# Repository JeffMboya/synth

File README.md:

<div align="center">

### Design circuit boards as code.

Turn text-based circuit designs into KiCad schematics, PCB layouts, and bills of materials.

Open source. Built for engineers and AI agents.

[Quick Start](#quick-start) · [Features](#features) · [Examples](#examples) · [Documentation](https://absmach.eu/docs/synth/user-guide/quick-start/) · [Contributing](#contributing)

</div>

## Introduction

Synth is an open-source compiler for electronic circuit boards. Describe your components, their connections, and board constraints in **SynthSpec**, a text-based design language. Synth checks the design and generates KiCad schematics, PCB layouts, and a bill of materials.

This brings a software development workflow to hardware: edit designs in your usual editor, review changes in Git, and run automated checks. Your `.synth` files capture the design intent; the schematic and board layout are generated outputs you can inspect in KiCad.

Engineers can use Synth from the command line. AI agents can use its **Model Context Protocol (MCP)** server to find components, validate circuits, and generate outputs through the same compiler, with structured diagnostics to guide corrections.

## Release checks

For CI and agent workflows, `synth check DESIGN.synth --json` is the single
deterministic, model-free gate for compiler validation and DRC. Add `--fab` to
require a complete KiCad manufacturing export and receive SHA-256 hashes for
the emitted files. A timed-out or unavailable physical stage is reported as
`unknown` and blocks the command; it is never treated as a pass.

Stages that shell out to `kicad-cli` are tri-state, because a check that
could not run is neither a pass nor a failure:

| Status    | Meaning                                                                 |
| --------- | ----------------------------------------------------------------------- |
| `pass`    | The tool ran and reported no blocking violations.                       |
| `fail`    | The tool ran and rejected the design.                                   |
| `unknown` | No evidence. Missing or unsupported `kicad-cli`, a missing symbol/footprint library, a crash, a timeout, or an unreadable report. |

`unknown` blocks exactly as `fail` does, and `--force` does not override it —
it overrides Synth's own findings, not the absence of verification. Likewise,
unconnected pads and KiCad DRC errors block a release export, and `--force`
does not override that. Each
`unknown` reports the tool, its version, the exact command, its stderr, and a
machine-stable reason (`not_installed`, `timeout`, `command_failed`,
`report_malformed`, `unsupported_version`, ...). `synth check --fab` embeds
that evidence under `stages.manufacturing.native`; `synth export-kicad
--verification-report FILE` writes it directly.

A plain `synth export-kicad` still works with no KiCad installed: it records
the `unknown` and sets `release_ready: false`, but does not block, since
nothing about that output claims to have been verified. Requesting
verification — `--validate-erc`, or any of `--gerbers`/`--drill`/`--step` —
makes an `unknown` blocking. Set `KICAD_CLI` to point at a specific build, and
`SYNTH_KICAD_CLI_TIMEOUT_SECS` to change the per-run budget (default 300s).

### Export overrides

`--force` and `--allow-unverified-parts` let development proceed past
findings that would otherwise stop an export. Every use is recorded in
`<out>/release.json` with the exact flag, the diagnostic it suppressed, the
affected parts, and the reviewer state of every part on the board:

| Field | Meaning |
| --- | --- |
| `release_ready` | `false` whenever any override was used. Derived, not settable. |
| `production_status` | `production` or `untrusted`. |
| `overrides[]` | flag, code, affected parts, and the consequence in plain words. |
| `reviewer_state[]` | per part: `reviewed_by`, `reviewed_at`, and whether it is reviewed. |

Human output on these paths leads with `UNTRUSTED / NOT FOR FABRICATION`.

`synth check --fab` reads that manifest and refuses a package carrying
overrides. To proceed, record who authorized it and why:

```bash
synth check DESIGN.synth --fab \
  --override-exception "prototype run, not customer hardware" \
  --authorized-by "a release manager"
```

An exception authorizes the run; it does not clean the package.
`release_ready` stays `false` and `production_status` stays `untrusted`,
because an authorization is a decision about risk rather than evidence the
risk is gone.

For CI and release gates, `synth export-kicad --safe` is the mode with no
override path: it refuses to sit beside `--force` or
`--allow-unverified-parts`, and then checks that the package it produced is
actually clean.

## Why Synth?

- **Review hardware changes in Git.** Components, connections, and constraints are text, making design intent visible in diffs and pull requests.
- **Check designs as you build.** Structured diagnostics identify problems and provide source locations and suggested fixes where available.
- **Keep outputs reproducible.** A typed compiler pipeline and deterministic placement and routing make generated artifacts repeatable.
- **Work with KiCad.** Export schematics, PCBs, and BOMs for inspection and downstream workflows.
- **Give agents concrete tools.** Expose validation, registry search, placement, routing, and export through MCP.

## How It Works

```mermaid
flowchart LR
    source["SynthSpec source"] --> compiler["Parse & resolve"]
    compiler --> checks["Validate"]
    checks --> layout["Place & route"]
    layout --> export["KiCad project & BOM"]
    checks --> feedback["Diagnostics & fixes"]
    feedback --> source
```

Synth resolves parts from a component registry and lowers the source into a typed board representation. Compiler stages use that shared representation for electrical checks, layout, routing, and export. A local browser viewer displays the schematic and diagnostics as you edit.

## Features

| Area               | Capabilities                                                                                                 |
| ------------------ | ------------------------------------------------------------------------------------------------------------ |
| Design language    | SynthSpec parser, typed board IR, components, connections, differential pairs, keepouts, and placement hints |
| Validation         | Electrical-rule checks, design-rule checks, structured diagnostics, and SMT-backed quantitative fixes        |
| Layout and routing | Deterministic schematic layout, component placement, and multilayer routing                                  |
| KiCad integration  | Project, schematic, PCB, and BOM export; optional fabrication outputs through `kicad-cli`                    |
| Component registry | Versioned parts, project and user overlays, search, import, and authoring tools                              |
| Developer tools    | CLI, live browser preview, JSON diagnostics, and an MCP server for agent integration                         |

## Quick Start

Use a current stable Rust toolchain with Cargo. Run the following from a local checkout:

```bash
git clone https://github.com/absmach/synth.git
cd synth
cargo build -p synth-cli
cargo run -p synth-cli -- --help
```

Validate the minimal example and export a KiCad project:

```bash
cargo run -p synth-cli -- validate fixtures/designs/hello.synth
cargo run -p synth-cli -- export-kicad fixtures/designs/hello.synth --out output/hello
```

The minimal example declares an empty two-layer board. Use the [example designs](#examples) to explore circuits with components and connections.

For machine-readable diagnostics:

```bash
cargo run -p synth-cli -- validate examples/env_logger.synth --format json
```

Open exported projects in KiCad. Optional Gerber, drill, and STEP exports require `kicad-cli`; see the [KiCad workflow guide](docs/kicad-workflows.md) for export and review details.

### Live Preview

Build the browser assets using the prerequisites and instructions in the [viewer guide](crates/synth-web/README.md), then run:

```bash
cargo run -p synth-cli -- preview examples/env_logger.synth
```

Open the local URL printed by the command. Save changes to the `.synth` file in your editor to refresh the schematic and diagnostics.

### Agent Integration

Start the MCP server over standard input and output:

```bash
cargo run -p synth-cli -- mcp --stdio
```

Agents can retrieve the SynthSpec language reference, search the registry, validate designs, apply fixes, and invoke compiler stages. See the [MCP guide](crates/synth-mcp/README.md) for transports and tool details.

## Examples

| Design                                                                     | What it demonstrates                                                          |
| -------------------------------------------------------------------------- | ----------------------------------------------------------------------------- |
| [Hello](fixtures/designs/hello.synth)                                      | The smallest board declaration                                                |
| [Environmental logger](examples/env_logger.synth)                          | USB-C power, a regulator, an MCU, an environmental sensor, and a debug header |
| [Sensor logger](examples/sensor_logger.synth)                              | A larger design with dual I²C sensors, SPI flash, and status LEDs             |
| [Placement and differential pairs](examples/placement_and_diff_pair.synth) | Placement hints, differential-pair constraints, and keepout regions           |

Additional language and validation cases live in [fixtures](fixtures/designs/README.md). Part definitions live in the [component registry](registry/README.md).

### RP2350 development-board agent workflow

The repository includes the placement and FreeRouting workflow used to develop
an RP2350-class board, including clean-netlist routing, zone refill, layer
normalization, and compact-outline support. See the [RP2350 agent workflow](docs/rp2350-agent-workflow.md)
for setup instructions, prompts, review commands, and the pre-generated review
artifact in [examples/rp2350](examples/rp2350/).

_Pre-generated compact RP2350 routed review artifact; open the [KiCad board](examples/rp2350/rp2350_devboard_freerouting_clean.kicad_pcb)
for an interactive review._

## Documentation

- [KiCad workflows](docs/kicad-workflows.md) — exported projects, validation, BOMs, and fabrication outputs.
- [RP2350 agent workflow](docs/rp2350-agent-workflow.md) — clean-netlist FreeRouting, compact outlines, agent setup, and review prompts.
- [Schematic procedures](docs/schematic-procedures.md) — schematic generation and review.
- [Diagnostic reference](docs/diagnostics/README.md) — diagnostic codes and repair guidance.
- [Diagnostic protocol](docs/protocol-v1.0.md) — the machine-readable diagnostic format.
- [Component registry](registry/README.md) — part definitions and registry structure.
- [Browser viewer](crates/synth-web/README.md) — build and run the live preview.
- [MCP server](crates/synth-mcp/README.md) — agent tools and integration.

## Contributing

Contributions to the compiler, component registry, examples, and documentation are welcome. Use [issues](https://github.com/absmach/synth/issues) to report bugs or discuss a change, and submit a pull request with a focused description and relevant validation.

Before submitting code, run the workspace checks:

```bash
make verify
```

This checks formatting, compilation, Clippy lints, the workspace tests, and registry tests. Run `make help` to see individual development commands.

## License

Synth is licensed under the [Apache License 2.0](LICENSE).

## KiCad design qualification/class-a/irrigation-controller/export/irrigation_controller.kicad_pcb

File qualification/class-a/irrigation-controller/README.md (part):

# Irrigation controller

A two-zone irrigation controller: 12 V in through a polyfuse, an AO3401A
reverse blocker with a gate clamp and an SMAJ13A TVS, an MP2307 buck to 3.3 V,
an STM32G030, two low-side solenoid drivers, two switched resistive soil probes,
a flow-pulse input, an I2C header, an ambient light sensor and an EEPROM, an SWD
header, and rail decoupling, bleeders, snubbers, indicator LEDs and test points.
Two layers, JLCPCB, 75.1 x 65.4 mm, 126 components. There is no humidity sensor
on the board: a breakout attaches to the I2C header at address 0x44.

**Status:** the board is routed and released (45 of 45 nets; KiCad 10.0.7 reports 0 errors,
0 unconnected pads and 0 `silk_overlap` warnings with the library tables), three fresh exports are
identical, and the exported KiCad files, the DRC and ERC reports, a fabrication package and a
reproduction script are committed ([`export/`](export/), [`reports/`](reports/), [`fab/`](fab/),
[`reproduce/`](reproduce/)). Since SammyOina's review of 2026-10-30 10:57: `C_IN1` and `C_IN2` sit
3.3 and 3.5 mm from the regulator's input pin `U1.2`, inside the placement review's 4 mm, and the
review flags no decoupling capacitor; the five `silk_overlap` warnings and the one ERC error (`power_pin_not_driven` on `+12V_VALVE`) are gone; the numbers, hashes, renders and
files below all come from one export. Not done: JLCPCB's PCB DFM of this exact package and the SMT DFM and
quote, which need an upload (see "JLCPCB DFM results"), and an independent review of two registry parts. Nothing
here was built or tested on hardware.

## How this board was made

An agent produced the design; Synth's own tools and scripts then packed and
tidied it, and a reviewer's list of faults was worked through. Every step is
logged under [`agent-run/`](agent-run/).

| Step | What ran | Result |
|---|---|---|
| 1. The design | An agent from one prompt ([`agent-run/prompt.md`](agent-run/prompt.md)), driving `synth mcp` with Read, Write and Edit only, from an empty workspace ([`report.md`](agent-run/report.md), [`tool-calls.md`](agent-run/tool-calls.md)) | 86 components |
| 2. Compaction | `synth_compact_layout` in `gap` mode | 75.1 x 65.4 mm after the later steps, released |
| 3. Fill | Two agent runs ([`fill-pass-prompt.md`](agent-run/fill-pass-prompt.md), reports [1](agent-run/fill-pass-report-1.md), [2](agent-run/fill-pass-report-2.md)): parts in the voids, each wired to a real function | 26 parts added |
| 4. Placement advice | [`tools/apply_advice_par.py`](agent-run/tools/apply_advice_par.py) applies Synth's placement advice in released steps | two passes, 15 and 18 moves kept |
| 5. Review fixes | An agent from [`prompt-1-review-fixes.md`](agent-run/review-fixes/prompt-1-review-fixes.md), report [`report-1-review-fixes.md`](agent-run/review-fixes/report-1-review-fixes.md): the clamps, the input TVS, the SHT30, the crystal load capacitors, the valve current, the schematic groups | source fixed; the board did not release |
| 6. Release search | Scripts ([`release_search.py`](agent-run/tools/release_search.py), [`fix_one.py`](agent-run/tools/fix_one.py), [`fix_pairs.py`](agent-run/tools/fix_pairs.py), [`verify_gap.py`](agent-run/tools/verify_gap.py)) that move one or two parts near a blocking finding and keep a move only if the export releases | released |
| 7. Input MOSFET | An agent from [`prompt-2-input-mosfet.md`](agent-run/review-fixes/prompt-2-input-mosfet.md), report [`report-2-input-mosfet.md`](agent-run/review-fixes/report-2-input-mosfet.md): `Q1` becomes an AO3401A (30 V) | released |
| 8. Fill again | An agent from [`prompt-3-fill.md`](agent-run/review-fixes/prompt-3-fill.md), report [`report-3-fill.md`](agent-run/review-fixes/report-3-fill.md): 18 parts, from values that already have a sourced part | 126 parts, 31.1 % fill |
| 9. Edits by the orchestrator | see below | final source and sidecar |
| 10. Final blockers | An agent from [`final-blockers/prompt.md`](agent-run/final-blockers/prompt.md) moved `D_TVS` ahead of `Q1` and rewrote the notes at 13.0 V; stopped when a stray quote in a note broke the source's syntax | source edit kept, quote repaired (below) |
| 11. Searches | [`final-blockers/tools/`](agent-run/final-blockers/tools/): decoupler placement on a x1.4 layout, then `R_NRST`, `C_NRST` and `SW_RESET` spots and pairs, a release search | none reached a released board with the decouplers at their pins (see "Open items") |
| 12. Silkscreen and vias | Synth commits `8052ca52`, `a38802ad` (silkscreen widened and cut back), `2ef37388` (0.2 mm drill, Synth PR #388), then on `SYN-case1-binary` the 0.25 mm clearance with 0.18 mm strokes and `7972c911` (test-point rings dropped) and `be19e90a` (pin-1 triangles dropped too) | in the exports below |
| 13. Input capacitors at the regulator pin | `C_IN1` and `C_IN2` change from a 1206 to an 0805 part (same 10 uF 25 V); [`make_room_search.py`](agent-run/tools/make_room_search.py) and [`tht_chain.py`](agent-run/tools/tht_chain.py) place them; Synth commits `ffa0c7ba` and `efb2f8be` on `SYN-case1-binary` clear the last silkscreen overlaps and `f7b110db` adds the missing power flag | both inside 4 mm of `U1.2`; 0 `silk_overlap`; 0 ERC errors; released |

### Edits applied by the orchestrator

Added 2026-10-31, after Sammy's review of 2026-10-30 10:57:

- Source: `C_IN1` and `C_IN2` changed from `c_generic_1206` to `c_generic_0805`, value `10uF 25V` unchanged, by `sed`, so that both fit within 4 mm of `U1.2`. The 0805 part is the Samsung CL21A106KAYNNNE (X5R, 25 V, +/-10 %, LCSC C15850). Samsung's catalogue gives no DC-bias curve, so the capacitance left at 13 V is not known; the rail also carries the 100 uF `C_BULK` and the fill capacitors `C_N7` and `C_N9`.
- Sidecar: `C_IN1` to (26.5, 13.6) turned 180 degrees (so its supply pad faces `U1.2`), `C_IN2` to (30.6, 13.6), `R_B1` to (42.3, 4.5) and `C_BULK` to x 38.25, by [`tht_chain.py`](agent-run/tools/tht_chain.py). It exports with the two capacitors at each of eight candidate pairs, moves a plain resistor or capacitor that ends under 2.2 mm from a through-hole pad to the nearest free spot, exports again, and keeps a chain only when it releases with no such pair (`C_BULK`'s x was set to where the exporter had already settled it). The 2.2 mm limit is 0.1 mm above the 2.1 mm that JLCPCB's DFM treats as a Danger.

The droplet's agent login hit its weekly usage limit, so these small edits were
made by script and checked by export. Each one changes position or group
membership only.

- Sidecar positions: `R_D1` to x 45.0, `R_FBB` to (34.9, 25.1), `C_BS` to (27.1, 15.5) and `L1` to (25.0, 20.3), each found by the release search above because it cleared a blocking finding; `J_SOIL1` restored to (42.5, 63.0), where the other two 3-pin connectors sit, after an earlier slide moved it 2 mm off its edge, and `R_N5` moved to (50.0, 60.5) so it no longer overlaps that connector's courtyard; `C_OUT2` to (41.25, 23.0), 11.6 mm from the regulator instead of 29 mm.
- Groups: the review and fill runs left 18 schematic groups; [`merge_groups_remove_part.py`](agent-run/tools/merge_groups_remove_part.py) (with `KEEP_TP_V1=1`) folds them into 13. No part, value or net changed.

- Source: the agent's note edit left a stray `"` after "valve loads." in the `R_B1` note, which made Synth report three parse errors and drop that note; the one character was removed.
- LEDs: `D_PWR` and `D_N2` changed from `led_green_0603` to the registry part `ltst_c190kgkt` (same footprint and pins), by `sed`; the old part is a NationStar NCD0603G1 with a forward voltage of 2.6 to 3.6 V, which cannot light from 3.3 V through 680 ohm.
- Netclasses: `via_diameter 0.6mm via_drill 0.2mm` added to `PWR12` and `PWR33`, and a `Default` class with the same.
- Sidecar: only `D_TVS` moved, from (27.5, 7.0) to (14.5, 7.5) (the agent, to sit at the input).
- Sidecar: `C_U4` moved from (55.0, 44.5) to (51.62, 41.78) and the test points `TP_SWDIO` from (71.5, 26.5) to (70.34, 26.81) and `TP_SWCLK` from (71.5, 31.5) to (70.3, 31.5), each found by a release search ([`tht_search.py`](agent-run/tools/tht_search.py) for the test points, which keeps a position only when the export still releases) to clear a JLCPCB finding.
- Sidecar: `C_U5` moved from (54.0, 56.0) to (54.64, 48.76), `C_IN1` from (31.0, 11.5) to (27.54, 13.19), `C_BS` from (27.1, 15.5) to (25.1, 15.5) and the fill capacitors `C_N13` from (54.5, 48.0) to (52.5, 39.0) and `C_N9` from (26.5, 13.0) to (23.0, 6.0), each by [`make_room_search.py`](agent-run/tools/make_room_search.py): it moves a decoupling capacitor to a spot near its supply pin and moves the parts that do not serve that IC out of the way (the named input and supply capacitors, the IC's own support parts and connectors never move), and keeps a move only when the export still releases and no through-hole to SMD gap falls under 2.4 mm.

The `.synth` source and the placement sidecar beside this file are the result.
The board needs Synth built from pull request #370 and the ones it stacks on
(#310, #345, #348, #352, #368), the silkscreen commits above (`SYN-silk-clear-of-vias`) and `SYN-case1-binary`, the drill change of #388, the parts of #326, and #266 for `polyfuse_1r5a`
and `l_1210_10uh`, which are not in the registry on `main`. `smaj13a_tvs` and
`p_mosfet_ao3401a` were authored for this board and are in `registry/parts/`;
neither has a reviewer recorded yet.

The server was KiCad 10.0.7 on a 16-vCPU machine, Synth built from
branch `SYN-case1-binary` (stacked on `SYN-silk-clear-of-vias`) at commit f7b110dbe0d4. `allow_incomplete` was never set, in any run log or
script.

## What was measured

All figures come from the files of the first of the three exports below
(KiCad 10.0.7, 16-vCPU server, Synth commit f7b110dbe0d4).

| | |
|---|---|
| Board | 75.1 x 65.4 mm, 4,912 mm2, two layers, 126 components (106 excluding holes and test points), 45 nets |
| Routing | state `routed`, 45 of 45 nets connected, 578 segments, 164 vias in the file (87 counted by the router), all 0.6 mm over a 0.2 mm drill (ring 0.20 mm); the project's `min_through_hole_diameter` is 0.2 and `min_via_diameter` 0.46 |
| KiCad DRC, 10.0.7, `--refill-zones --severity-all`, with the KiCad footprint library table | 0 errors, 0 unconnected, 120 warnings, all `lib_footprint_mismatch` (below); 0 `silk_overlap`. Report: [`reports/kicad_drc.json`](reports/kicad_drc.json) |
| Router and release gate | `release_ready` true, no blocking reason, no via in a pad, no unresolved return via |
| Trace width, as routed | `VIN_FUSED`, `VALVE1_SW`, `VALVE2_SW` 0.8 mm; `+12V_VALVE` 0.4 to 0.8 mm; `+3V3` 0.2 to 0.4 mm |
| Silkscreen | the export's own summary: 751 strokes widened to 0.18 mm; 300 outline lines cut back 0.25 mm from vias and pads; 25 silkscreen circles and polygons dropped (16 test-point rings, 9 pin-1 triangles); 37 labels moved and 13 hidden because no spot clear of copper and of other silkscreen was within reach |
| BOM | 126 rows, every one with a manufacturer, MPN, distributor, order number and page (below) |
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
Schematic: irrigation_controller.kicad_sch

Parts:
C_B1, C_B2, C_B3, C_B4: 100nF; C_0603_1608Metric
C_B5, C_B8: 4.7uF; C_0805_2012Metric
C_BS: 10nF; C_0603_1608Metric
C_BULK: 100uF 25V; CP_Radial_D6.3mm_P2.50mm
C_COMP: 2.2nF; C_0603_1608Metric
C_F1, C_F2: 10nF; C_0603_1608Metric
C_FL: 10nF; C_0603_1608Metric
C_IN1, C_IN2: 10uF 25V; C_0805_2012Metric
C_N1, C_N2, C_N3, C_N4, C_N8, C_N9, C_N11, C_N12, C_N13: 100nF; C_0603_1608Metric
C_N5: 10uF; C_0805_2012Metric
C_N6, C_N10, C_N14: 4.7uF; C_0805_2012Metric
C_N7: 10uF 25V; C_0805_2012Metric
C_NRST: 100nF; C_0603_1608Metric
C_OUT1, C_OUT2: 22uF 10V; C_1206_3216Metric
C_SN1, C_SN2: 10nF; C_0603_1608Metric
C_SS: 100nF; C_0603_1608Metric
C_U4, C_U5: 100nF; C_0603_1608Metric
C_VDD1: 100nF; C_0603_1608Metric
C_VDD2: 4.7uF; C_0805_2012Metric
C_X1, C_X2: 6.2pF; C_0603_1608Metric
D_FLY1, D_FLY2: 1N5819; D_SOD-123; MPN 1N5819; LCSC C8224
D_FZ: (no value); D_SOD-123
D_N1: (no value); LED_0603_1608Metric
D_N2: LTST-C190KGKT; LED_0603_1608Metric; MPN LTST-C190KGKT
D_PWR: LTST-C190KGKT; LED_0603_1608Metric; MPN LTST-C190KGKT
D_QG: (no value); D_SOD-123
D_TVS: SMAJ13A; D_SMA; MPN SMAJ13A
D_VALVE: (no value); LED_0603_1608Metric
F1: 1812L150/16DR; Fuse_1812_4532Metric; MPN 1812L150/16DR; LCSC C207070
H1, H2, H3, H4: (no value); MountingHole_2.5mm
J1: (no value); JST_XH_S2B-XH-A-1_1x02_P2.50mm_Horizontal
J_FLOW: (no value); JST_PH_S3B-PH-K_1x03_P2.00mm_Horizontal
J_I2C: (no value); JST_PH_S4B-PH-K_1x04_P2.00mm_Horizontal
J_SOIL1, J_SOIL2: (no value); JST_PH_S3B-PH-K_1x03_P2.00mm_Horizontal
J_SWD: (no value); PinHeader_1x05_P2.54mm_Vertical
J_VALVE1, J_VALVE2: (no value); JST_XH_S2B-XH-A-1_1x02_P2.50mm_Horizontal
L1: CBC3225T100MR; L_1210_3225Metric; MPN CBC3225T100MR; LCSC C90315
Q1: AO3401A; SOT-23; MPN AO3401A
Q_E1, Q_E2: (no value); SOT-23
Q_V1, Q_V2: AO3400A; SOT-23; MPN AO3400A
R_B1, R_B2: 100k; R_0603_1608Metric
R_B3, R_B4: 47k; R_0603_1608Metric
R_COMP: 9.1k; R_0603_1608Metric
R_D1, R_D2: 10k; R_0603_1608Metric
R_EN: 100k; R_0603_1608Metric
R_EPU1, R_EPU2: 100k; R_0603_1608Metric
R_F1, R_F2: 1k; R_0603_1608Metric
R_FBB: 10k; R_0603_1608Metric
R_FBT: 26.1k; R_0603_1608Metric
R_FPU: 10k; R_0603_1608Metric
R_FS: 2.2k; R_0603_1608Metric
R_G1, R_G2: 100; R_0603_1608Metric
R_LV: 680; R_0603_1608Metric
R_N1, R_N5, R_N6: 100k; R_0603_1608Metric
R_N2: 47k; R_0603_1608Metric
R_N3: 2.2k; R_0603_1608Metric
R_N4: 680; R_0603_1608Metric
R_NRST: 10k; R_0603_1608Metric
R_PD1, R_PD2: 100k; R_0603_1608Metric
R_PWR: 680; R_0603_1608Metric
R_QG: 10k; R_0603_1608Metric
R_S1, R_S2: 1k; R_0603_1608Metric
R_SCL: 4.7k; R_0603_1608Metric
R_SDA: 4.7k; R_0603_1608Metric
R_SN1, R_SN2: 100; R_0603_1608Metric
SW_RESET: (no value); SW_SPST_PTS645Sx43SMTR92
TP_3V3, TP_12V: (no value); TestPoint_Pad_D1.5mm
TP_FLOW: (no value); TestPoint_Pad_D1.5mm
TP_GND: (no value); TestPoint_Pad_D1.5mm
TP_N1, TP_N2: (no value); TestPoint_Pad_D1.5mm
TP_NRST: (no value); TestPoint_Pad_D1.5mm
TP_SCL: (no value); TestPoint_Pad_D1.5mm
TP_SDA: (no value); TestPoint_Pad_D1.5mm
TP_SOIL1, TP_SOIL2: (no value); TestPoint_Pad_D1.5mm
TP_SWCLK: (no value); TestPoint_Pad_D1.5mm
TP_SWDIO: (no value); TestPoint_Pad_D1.5mm
TP_V1, TP_V2: (no value); TestPoint_Pad_D1.5mm
TP_VIN: (no value); TestPoint_Pad_D1.5mm
U1: MP2307DN-LF-Z; SOIC-8-1EP_3.9x4.9mm_P1.27mm_EP2.41x3.3mm; MPN MP2307DN-LF-Z; LCSC C18921
U2: (no value); LQFP-32_7x7mm_P0.8mm
U4: (no value); Broadcom_APDS-9301
U5: (no value); SOIC-8_3.9x4.9mm_P1.27mm
Y1: NX3225GD-8MHZ-STD-CRA-3; Crystal_SMD_3225-4Pin_3.2x2.5mm; MPN NX3225GD-8MHZ-STD-CRA-3

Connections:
+3V3: C_B2.1, C_B4.1, C_B5.1, C_B8.1, C_N1.1, C_N2.1, C_N3.1, C_N4.1, C_N5.1, C_N6.1, C_N8.1, C_N10.1, C_N11.1, C_N12.1, C_N13.1, C_N14.1, C_OUT1.1, C_OUT2.1, C_U4.1, C_U5.1, C_VDD1.1, C_VDD2.1, J_I2C.2, J_SWD.1, L1.2, Q_E1.2 (s), Q_E2.2 (s), R_B2.1, R_B4.1, R_EPU1.1, R_EPU2.1, R_FBT.1, R_FPU.1, R_N1.1, R_N2.1, R_N4.1, R_NRST.1, R_PWR.1, R_SCL.1, R_SDA.1, TP_3V3.1, TP_N1.1, U2.4 (VDD), U4.1 (VDD), U5.8 (VCC)
+12V_VALVE: C_B1.1, C_B3.1, C_BULK.1, C_IN1.1, C_IN2.1, C_N7.1, C_N9.1, D_FLY1.1 (K), D_FLY2.1 (K), D_QG.1 (K), J_FLOW.1, J_VALVE1.1, J_VALVE2.1, Q1.2 (s), R_B1.1, R_B3.1, R_EN.1, R_N3.1, R_N5.1, R_N6.1, R_SN1.1, R_SN2.1, TP_12V.1, U1.2 (in)
BUCK_BS: C_BS.1, U1.1 (bs)
BUCK_COMP: R_COMP.1, U1.6 (comp)
BUCK_COMPC: C_COMP.1, R_COMP.2
BUCK_EN: R_EN.2, U1.7 (en)
BUCK_FB: R_FBB.1, R_FBT.2, U1.5 (fb)
BUCK_SS: C_SS.1, U1.8 (ss)
BUCK_SW: C_BS.2, L1.1, U1.3 (sw)
FLOW_IN: J_FLOW.3, R_FPU.2, R_FS.1
FLOW_PULSE: C_FL.1, D_FZ.1 (K), R_FS.2, TP_FLOW.1, U2.13 (PA6)
GND: C_B1.2, C_B2.2, C_B3.2, C_B4.2, C_B5.2, C_B8.2, C_BULK.2, C_COMP.2, C_F1.2, C_F2.2, C_FL.2, C_IN1.2, C_IN2.2, C_N1.2, C_N2.2, C_N3.2, C_N4.2, C_N5.2, C_N6.2, C_N7.2, C_N8.2, C_N9.2, C_N10.2, C_N11.2, C_N12.2, C_N13.2, C_N14.2, C_NRST.2, C_OUT1.2, C_OUT2.2, C_SS.2, C_U4.2, C_U5.2, C_VDD1.2, C_VDD2.2, C_X1.2, C_X2.2, D_FZ.2 (A), D_N1.1 (K), D_N2.1 (K), D_PWR.1 (K), D_TVS.2 (A), D_VALVE.1 (K), J1.2, J_FLOW.2, J_I2C.1, J_SOIL1.3, J_SOIL2.3, J_SWD.3, Q_V1.2 (S), Q_V2.2 (S), R_B1.2, R_B2.2, R_B3.2, R_B4.2, R_D1.2, R_D2.2, R_FBB.2, R_N1.2, R_N2.2, R_N5.2, R_N6.2, R_PD1.2, R_PD2.2, R_QG.2, SW_RESET.2, TP_GND.1, TP_N2.1, U1.4 (gnd), U1.9 (ep), U2.5 (VSS), U4.2 (GND), U4.3 (ADR_SEL), U5.1 (A0), U5.2 (A1), U5.3 (A2), U5.4 (GND), U5.7 (WP), Y1.2 (G), Y1.4 (G)
I2C_SCL: J_I2C.4, R_SCL.2, TP_SCL.1, U2.30 (PB6), U4.4 (SCL), U5.6 (SCL)
I2C_SDA: J_I2C.3, R_SDA.2, TP_SDA.1, U2.31 (PB7), U4.5 (SDA), U5.5 (SDA)
LED_N12_A: D_N1.2 (A), R_N3.2
LED_N33_A: D_N2.2 (A), R_N4.2
LED_PWR_A: D_PWR.2 (A), R_PWR.2
LED_VALVE_A: D_VALVE.2 (A), R_LV.2
LED_VALVE_DRV: R_LV.1, U2.14 (PA7)
NRST: C_NRST.1, J_SWD.5, R_NRST.2, SW_RESET.1, TP_NRST.1, U2.6 (NRST)
OSC_IN: C_X1.1, U2.2 (PC14), Y1.1
OSC_OUT: C_X2.1, U2.3 (PC15), Y1.3
Q1_GATE: D_QG.2 (A), Q1.1 (g), R_QG.1
SNUB1: C_SN1.1, R_SN1.2
SNUB2: C_SN2.1, R_SN2.2
SOIL1_ADC: C_F1.1, R_F1.2, TP_SOIL1.1, U2.9 (PA2)
SOIL1_EXC: Q_E1.3 (d), R_S1.1
SOIL1_EXC_EN: Q_E1.1 (g), R_EPU1.2, U2.11 (PA4)
SOIL1_PROBE: J_SOIL1.1, R_S1.2
SOIL1_SENSE: J_SOIL1.2, R_D1.1, R_F1.1
SOIL2_ADC: C_F2.1, R_F2.2, TP_SOIL2.1, U2.10 (PA3)
SOIL2_EXC: Q_E2.3 (d), R_S2.1
SOIL2_EXC_EN: Q_E2.1 (g), R_EPU2.2, U2.12 (PA5)
SOIL2_PROBE: J_SOIL2.1, R_S2.2
SOIL2_SENSE: J_SOIL2.2, R_D2.1, R_F2.1
SWCLK: J_SWD.4, TP_SWCLK.1, U2.25 (PA14)
SWDIO: J_SWD.2, TP_SWDIO.1, U2.24 (PA13)
VALVE1_GATE: R_G1.1, U2.27 (PB3)
VALVE1_GATE_Q: Q_V1.1 (G), R_G1.2, R_PD1.1
VALVE1_SW: C_SN1.2, D_FLY1.2 (A), J_VALVE1.2, Q_V1.3 (D), TP_V1.1
VALVE2_GATE: R_G2.1, U2.28 (PB4)
VALVE2_GATE_Q: Q_V2.1 (G), R_G2.2, R_PD2.1
VALVE2_SW: C_SN2.2, D_FLY2.2 (A), J_VALVE2.2, Q_V2.3 (D), TP_V2.1
VIN_12V_RAW: F1.1, J1.1
VIN_FUSED: D_TVS.1 (K), F1.2, Q1.3 (d), TP_VIN.1

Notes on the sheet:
POWER INPUT
BUCK 3V3
MCU
VALVE 1
VALVE 2
SOIL 1
SOIL 2
FLOW
I2C SENSORS
LEDS
3V3 RAIL DECOUPLING
12V RAIL DECOUPLING
TEST POINTS AND MOUNTING
J1 JST XH S2B-XH-A: pin1 VIN_12V_RAW, pin2 GND. Mate with XHP-2 housing. Pin 1 is the +12 V pin.
F1 1.5 A hold PPTC, then Q1 AO3401A P-FET (30 V Vds, 12 V Vgs max, 4 A) reverse-polarity switch (body diode to start, Vgs clamped to -5.1 V by D_QG).
Q1 gate check: the 5.1 V zener D_QG across source and gate limits Vgs to about 5.1 V, within the AO3401A 12 V gate-source rating. The drain sees at most the TVS clamp of 21.5 V (D_TVS is upstream of Q1), below the AO3401A 30 V drain-source rating by 8.5 V.
D_TVS SMAJ13A (Littelfuse, 400 W, VR 13.0 V, VBR 14.40 to 15.90 V at 1 mA, IR 1 uA maximum at VR, VC 21.5 V at IPP 18.6 A) sits on VIN_FUSED, before Q1: its cathode joins the fused input net on the Q1 drain side and its anode is on GND, so a surge is clamped before it reaches Q1, the buck or any ca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
TVS check: the supply maximum is 13.0 V, equal to the 13.0 V standoff VR, so leakage at the maximum input is the datasheet IR of 1 uA maximum, and 13.0 V is 1.4 V below the 14.40 V minimum breakdown. Worst-case clamp 21.5 V is below the MP2307 recommended input maximum 23 V by 1.5 V and its absolut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
MP2307 (internal sync rectifier, 340 kHz). Vout = 0.925 V x (1 + 26.1k/10k) = 3.34 V.
L1 10 uH: ripple about 0.7 A p-p at 12 V in; confirm L1 saturation current against its datasheet.
J_SWD pin1 +3V3, pin2 SWDIO, pin3 GND, pin4 SWCLK, pin5 NRST. No USB bootloader; program over SWD.
HSE 8 MHz on PC14/PC15 (OSC_IN/OSC_OUT). Crystal NDK NX3225GD-8MHZ-STD-CRA-3, CL 8 pF. CL = (C1 x C2)/(C1 + C2) + Cstray with Cstray 5 pF, so C1 = C2 = 2 x (8 - 5) = 6 pF. Nearest standard value (E24) 6.2 pF: CL = 6.2/2 + 5 = 8.1 pF, 0.1 pF from 8 pF (limit 0.5 pF). Cstray 5 pF is an assumption, no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
Boot: PA14 (SWCLK) is BOOT0; default option bytes boot from flash.
J_VALVE1 pin1 +12V_VALVE, pin2 VALVE1_SW (low-side). Flyback cathode to +12V_VALVE.
Load: 12 V DC solenoid, coil current at most 0.5 A. AO3400A carries 0.5 A (rated far above, needs datasheet value sourcing for the exact figure), flyback diode 1N5819-class (1 A class), VALVE1_SW is class PWR12 (0.8 mm, about 8x the width a 0.5 A / 10 C rise needs).
J_VALVE2 pin1 +12V_VALVE, pin2 VALVE2_SW (low-side). Flyback cathode to +12V_VALVE.
Load: 12 V DC solenoid, coil current at most 0.5 A. Same checks as valve 1: MOSFET, flyback diode and PWR12 tracks carry 0.5 A.
R_SN2 100 ohm in series with C_SN2 10 nF is an RC snubber across the valve 2 coil connector. TP_V2 probes VALVE2_SW. C_B3 100 nF bypasses +12V_VALVE beside the valve 2 driver; R_B3 47 k bleeds the 12 V rail: 13.0 V / 47 k = 0.277 mA, 3.6 mW.
J_SOIL1 pin1 excitation, pin2 sense, pin3 GND. Probe between pins 1 and 2. Excitation off by default (gate pulled to +3V3).
J_SOIL2 pin1 excitation, pin2 sense, pin3 GND. Probe between pins 1 and 2. Excitation off by default (gate pulled to +3V3).
J_FLOW pin1 +12V_VALVE sensor supply, pin2 GND, pin3 pulse. Open-collector assumed; 3.3 V zener D_FZ (cathode on FLOW_PULSE, anode on GND) behind R_FS 2.2 k clamps a push-pull output to the STM32G030 input range. Current at a 13.0 V sensor output: (13.0 - 3.3) / 2.2 k = 4.41 mA (12 V: 3.95 mA), abo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
Addresses: APDS-9301 0x29 (ADR_SEL low), 24LC256 0x50 (A2..A0 low). No collisions. An SHT30 breakout attaches to J_I2C at address 0x44, which stays free; the on-board SHT30 was removed because its 0.5 mm DFN cannot be escaped on two layers.
J_I2C pin1 GND, pin2 +3V3, pin3 SDA, pin4 SCL. 3.3 V only, no 5 V; external load <= 100 mA.
D_PWR lit when +3V3 is present. D_VALVE lit when firmware commands either valve on.
D_N1 lit when +12V_VALVE is present (R_N3), D_N2 lit when +3V3 is present (R_N4).
LED currents are I = (V - Vf) / R; the Vf of the selected LEDs is not yet read from their datasheets (needs sourcing), so the upper bound with Vf = 0 is given and the real current is lower. D_PWR, R_PWR 680: at most 3.3 V / 680 = 4.85 mA. D_VALVE, R_LV 680, driven from MCU pin PA7 at 3.3 V: at most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
+3V3 bulk and high-frequency decoupling; R_N1 and R_N2 are bleeders across +3V3.
C_B8 4.7 uF adds bulk decoupling to +3V3 beside the MCU. C_B2 and C_B4 100 nF plus C_B5 4.7 uF add high-frequency and bulk decoupling to +3V3 near the I2C parts. R_B2 100 k and R_B4 47 k are bleeders across +3V3 (3.3 V / 100 k = 33 uA and 3.3 V / 47 k = 70 uA); R_N1 100 k and R_N2 47 k give the sam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
+12V_VALVE decoupling and bleeders.
R_B1 bleeds C_BULK (100 k, 13.0 V / 100 k = 0.130 mA). R_N5 and R_N6 are 100 k bleeders on the same rail, 0.130 mA each. Resistive bleed of the +12V_VALVE rail: R_N5, R_N6, R_B1 (100 k each) and R_B3 (47 k) in parallel are 19.5 k, 0.67 mA at 13.0 V; with R_EN 100 k to the buck enable 16.3 k. C_BULK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

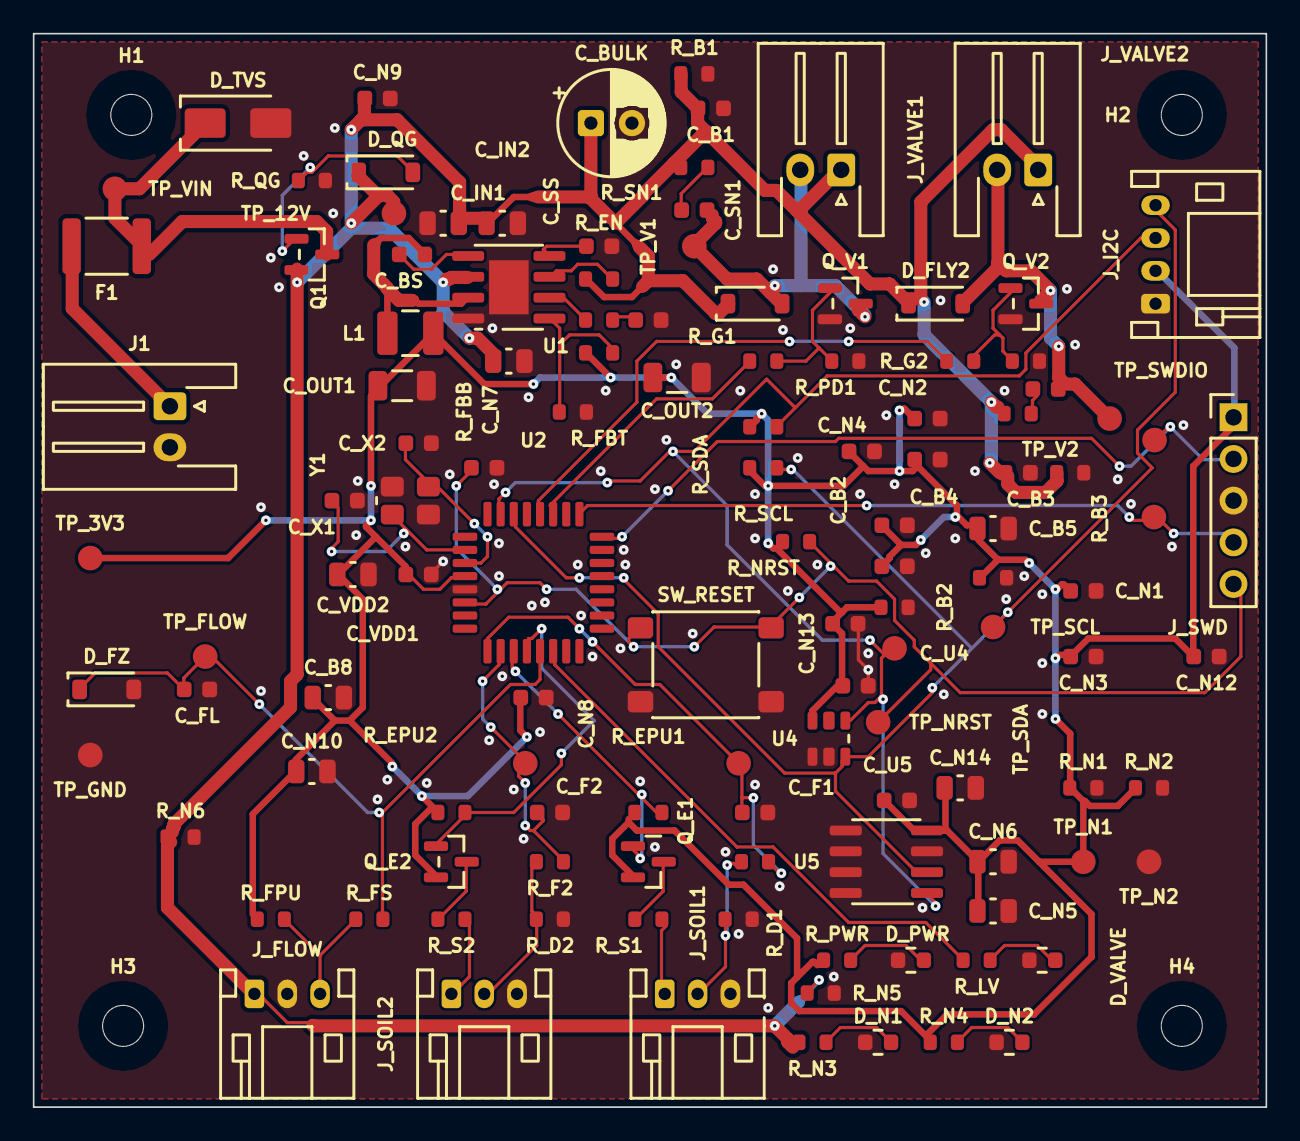
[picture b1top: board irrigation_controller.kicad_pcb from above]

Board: 2 copper layers, 75.1 x 65.4 mm, 126 parts (0 on the bottom side), 45 nets.

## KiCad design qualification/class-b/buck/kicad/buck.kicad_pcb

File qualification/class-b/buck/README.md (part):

# 24 V in, 3.3 V out buck with input parts (PTC, reverse-block diode, TVS) (SYN-67)

Status: designed, placed, routed, DRC and ERC counted, Gerber and drill files generated. Not fabricated,
not powered, no hardware test. All 8 new parts are UNVERIFIED (imported, no reviewer). No reviewer has
signed off this board, so the fab package reports `release_ready: false` by design.
Intended for 24 V +10% in and 1 A out. The converter is rated 4 A and the estimate supports 2 A, but the
PTC and the input connector set the 1 A rating (see Limits). No surge rating: the TVS clamp is above the
converter's absolute maximum.

## Purpose

Ticket #67 under #38 (Class B qualification): a switching-regulator board with input and output filtering,
feedback, power-good and thermal copper, plus a negative variant that the feedback-safety rule
(E-SYNTH-POWER-011, PR #56) must flag.

## What

- `buck.synth`, negative `buck_neg_fb_sw.synth`, hashes in `SHA256SUMS`, matrix and `#38` traceability in `QUALIFICATION.md`, evidence in `kicad/`, `reports/`, `images/`.
- `kicad/`: the KiCad project, BOM, pick-and-place, `gerbers/` (22 Gerbers plus the job file, 4 copper layers) and `drill/` (PTH and NPTH). `reports/`: `release.json` (source/DRC gate) and `release-fab.json` (fab package, untrusted), DRC, ERC, routing and connectivity.
- Chain: J1 (JST XH) -> F1 PTC -> D1 SS36 Schottky (reverse block) -> VIN node.
  VIN node: D2 SMBJ30A TVS, C1 47 uF bulk, C2 10 uF, C3 220 nF (on the U1 VIN pin), U1 LMR33640, UVLO divider.
- U1 -> L1 6.8 uH -> C5, C6, C9 (3x 22 uF, 25 V X7R) -> J2. C4 100 nF boot, C8 1 uF on VCC.
- Feedback: R_FB_T 100k from the output node (L1 pad 2 side), R_FB_B 43.2k, C7 56 pF across R_FB_T.
  Vout = 1.0 x (1 + 100k/43.2k) = 3.315 V typical, 3.26 to 3.36 V over Vref 0.985 to 1.015 V (ideal resistors).
- Power-good: U1 pin 4 is open drain, pulled up to +3V3 through R_PG 100k and brought out on J2 pin 3. D4 (green, "PG FAULT") and R_PGLED 470 R run from +3V3 to PG, so the LED lights while PG is low and stays dark while power is good.
- Thermal: U1 pin 9 is a 2.41 x 3.1 mm exposed pad soldered to the F.Cu GND pour (see Thermal).
- Negative file: identical except R_FB_T and C7 hang from SW. Besides E-SYNTH-POWER-011 it emits the same warnings as the good board except 1 fewer E-SYNTH-SCHEM-004 and 1 fewer E-SYNTH-SCHEM-005 (20 against 22).
- Board: 60.75 x 31.855 mm (1935 mm2), 4 layers, GND pours on all layers. Power tracks 0.5 mm, signal
  0.127 mm. The board grew from 1891 mm2 (SOT-23-6 converter, no PG, no mounting holes) because the
  HSOP-8 package, the fourth output capacitor, the VCC capacitor and the two mounting holes need room.
- Two M2.5 non-plated mounting holes (H1, H2) in opposite corners.

## UVLO (LMR33640 SNVSB99C section 9.2.2.9, Eq 10)

Datasheet values: VEN-H 1.2 / 1.231 / 1.26 V (min/typ/max), hysteresis 100 mV. RENB = R_UV_B = 100k, RENT = R_UV_T = 1.37M.
- Start = VEN-H x (1 + RENT/RENB) = 1.231 x (1 + 13.7) = 18.09 V.
- Stop = Start x (1 - VEN_HYS/VEN-H) = 18.09 x (1 - 0.1/1.231) = 16.62 V.
- 1% resistors, typical threshold: start 17.8 to 18.4 V, stop 16.3 to 16.9 V.
- EN at 28 V in is 28 x 0.1/1.47 = 1.90 V; the EN absolute maximum is VIN + 0.3 V.

## Power-good

| Item | Value | Source |
| --- | --- | --- |
| Pin | U1 pin 4, open-drain NMOS | SNVSB99C 8.3.1 |
| Pull-up | R_PG 100k to +3V3 | 8.3.1 suggests 100k to VCC or VOUT |
| Sink current | 33 uA through 100k, limit 5 mA | 8.3.1 |
| Asserted low | during start-up, current limit and thermal shutdown | 8.3.1 |
| Released high | Vout inside 95/105% (typ), 93/107% over limits | 7.5, Figure 8-1 |
| Start-up delay | about 4 ms from EN asserted | 8.3.1 |
| Glitch filter | output excursions shorter than tPG do not trip it | 8.3.1 |
| Presented on | J2 pin 3 (3.3 V logic) | this board |

The netlist proves the connection (A15 in `QUALIFICATION.md`). Nothing proves the thresholds, the delay or
the behaviour on a fault: Synth has no power-good rule (`synth capability list` marks
`power_sequencing_and_power_good` unsupported), and this board was not powered.

## Thermal

- U1's exposed pad (pin 9, 2.41 x 3.1 mm) is soldered to the F.Cu GND pour. The pour is stitched to the
  inner ground planes by 16 GND vias; 1 of them is within 4 mm of the pad edge.
- There are no vias **in** the pad. The board's fabrication floor is a 0.3 mm drill (the exported
  `.kicad_pro` says `min_through_hole_diameter 0.3`), and every KiCad HSOP-8 thermal-via footprint ships
  0.2 mm drills, so that footprint was not used.
- Estimate, not a measurement: TI Figure 9-3 gives about 38 C/W for the DDA package on a four-layer board
  with 20 to 24 cm2 of copper per layer, and this board has 22.4 cm2. At 1 A out with the assumed 85%
  efficiency the loss is 3.3/0.85 - 3.3 = 0.58 W, so the junction is about 70 + 22 = 92 C. At 2 A out the
  loss is 1.17 W and the junction about 114 C. Both are under the 125 C limit, but the efficiency is an
  assumption and the copper-area curve is not a board-level simulation.
- TI's `RthetaJA` table value is deliberately not used: the datasheet says it is not valid for design.

## Parts and datasheets (read with curl + pdftotext, 2026-10-24)

| Part | Datasheet | Revision | Values taken | Conflict or gap |
| --- | --- | --- | --- | --- |
| U1 TI LMR33640ADDA (HSOIC-8 DDA) | https://www.ti.com/lit/ds/symlink/lmr33640.pdf | SNVSB99C, Nov 2020 | 3.8-36 V recommended, 38 V abs max; 4 A; 400 kHz; internal compensation; VFB 0.985/1.0/1.015 V; pins 1 GND, 2 VIN, 3 EN, 4 PG, 5 FB, 6 VCC, 7 BOOT, 8 SW, 9 EP; Table 9-2 at 3.3 V/400 kHz: L 6.8 uH, Cout 4x22 uF typical (3x22 minimum), Cin 10 uF + 220 nF, Rfbt 100k, Rfbb 4.32k (Table 9-3 says 43.3k), Cboot 100 nF, Cvcc 1 uF; PG open drain, 4 ms start-up delay, 93/95/105/107% thresholds; thermal pad on pin 9 | Table 9-2's Rfbb of 4.32k contradicts Eq 3 and Table 9-3; 43.2k is used here. KiCad symbol LMR33640ADDA has the pin order of the physical package, not the symbol drawing |
| L1 Bourns SRN6045TA-6R8M | https://www.bourns.com/docs/Product-Datasheets/SRN6045TA.pdf | REV. 06/24 (footer) | 6.8 uH +-20%, DCR 34 mOhm typ, Irms 3.6 A, Isat 5.7 A (L -30%), 6.0 x 6.0 mm | Registry has no Isat field; Isat is in the description |
| D1 Vishay SS36 | https://www.vishay.com/docs/88751/ss32.pdf | 23-Apr-2020 (doc 88751) | VRRM 60 V, 3 A, IFSM 100 A, VF 0.75 V max at 3 A, IR 0.5 mA at 25 C and 10 mA at 100 C, SMC | KiCad `Diode:SS36` defaults to SMA, this sheet is SMC (SMC used). VF at low current not read |
| D2 Vishay SMBJ30A | https://www.vishay.com/docs/88392/smbj.pdf | 09-Jan-2024 (doc 88392) | 600 W 10/1000 us, VWM 30 V, VBR 33.3-36.8 V at 1 mA, VC 48.4 V at 12.4 A, VBR temperature coefficient 0.099 %/C, SMB | No KiCad SMBJ30A symbol; Device:D_Zener used. Registry `max_voltage_v` 30 is VWM. The clamp is above U1's 38 V absolute maximum, so this part is not an OVP |
| F1 Bourns MF-MSMF110/33X | https://www.bourns.com/docs/Product-Datasheets/mfmsmf.pdf | REV. BE, 09/26 (footer) | Vmax 33 V, Imax 20 A, Ihold 1.1 A at 23 C, 0.93 A at 40 C, 0.73 A at 60 C, 0.63 A at 70 C, 0.50 A at 85 C, Itrip 2.2 A, R 0.06-0.20 Ohm | none found. Registry `max_current_ma` 1100 is Ihold at 23 C |
| J1, J2 JST B2B-XH-A / B4B-XH-A | https://www.jst-mfg.com/product/pdf/eng/eXH.pdf | none printed | 2.5 mm pitch, 3 A, 250 V | Existing registry `jst_xh_2pin`/`jst_xh_4pin` say 5 V / 100 mA; that conflicts with this sheet, so new parts were added |
| D3 Lite-On LTST-C190KGKT | https://optoelectronics.liteon.com/upload/download/DS22-2000-074/LTST-C190KGKT.PDF | not checked | none (existing registry part) | Site unreachable (curl code 000) |
| C1 47 uF | Honor Elec RVT1H470M0810 (JLCPCB C2895739) | [LCSC datasheet](https://wmsc.lcsc.com/wmsc/upload/file/pdf/v2/lcsc/2109290630_Honor-Elec-RVT1H470M0810_C2895739.pdf) | 47 uF, 50 V, +/-20 %, 105 C, 8 x 10.2 mm SMD; ripple 120 mA at 120 Hz | ESR not given |
| C2, C5, C6, C9 (1206), C3, C4, C7, C8 (0603), resistors | none | | generic registry parts; voltage and dielectric are set per instance in `buck.synth` | no MPN. Murata and TDK pages returned 404/403/500: no DC-bias data |

## Limits and honesty notes

- Overvoltage: the converter is rated to 36 V recommended / 38 V absolute maximum, so a **sustained**
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
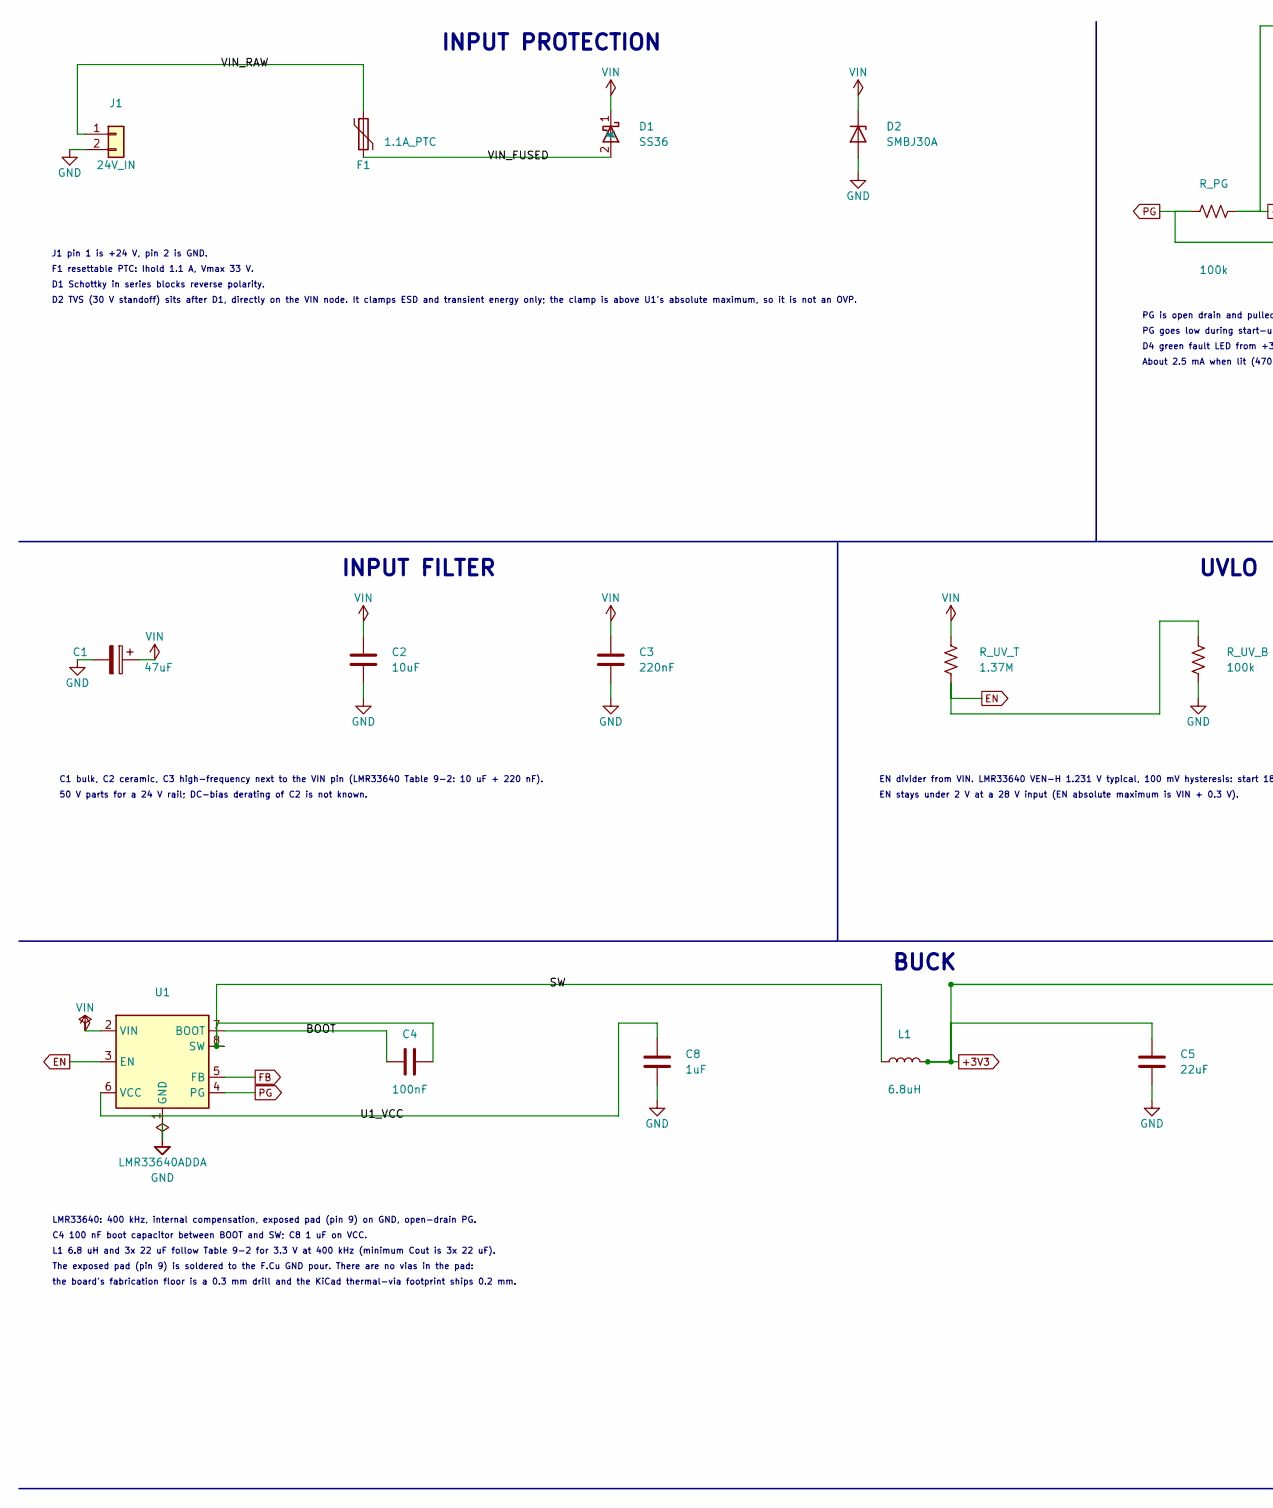
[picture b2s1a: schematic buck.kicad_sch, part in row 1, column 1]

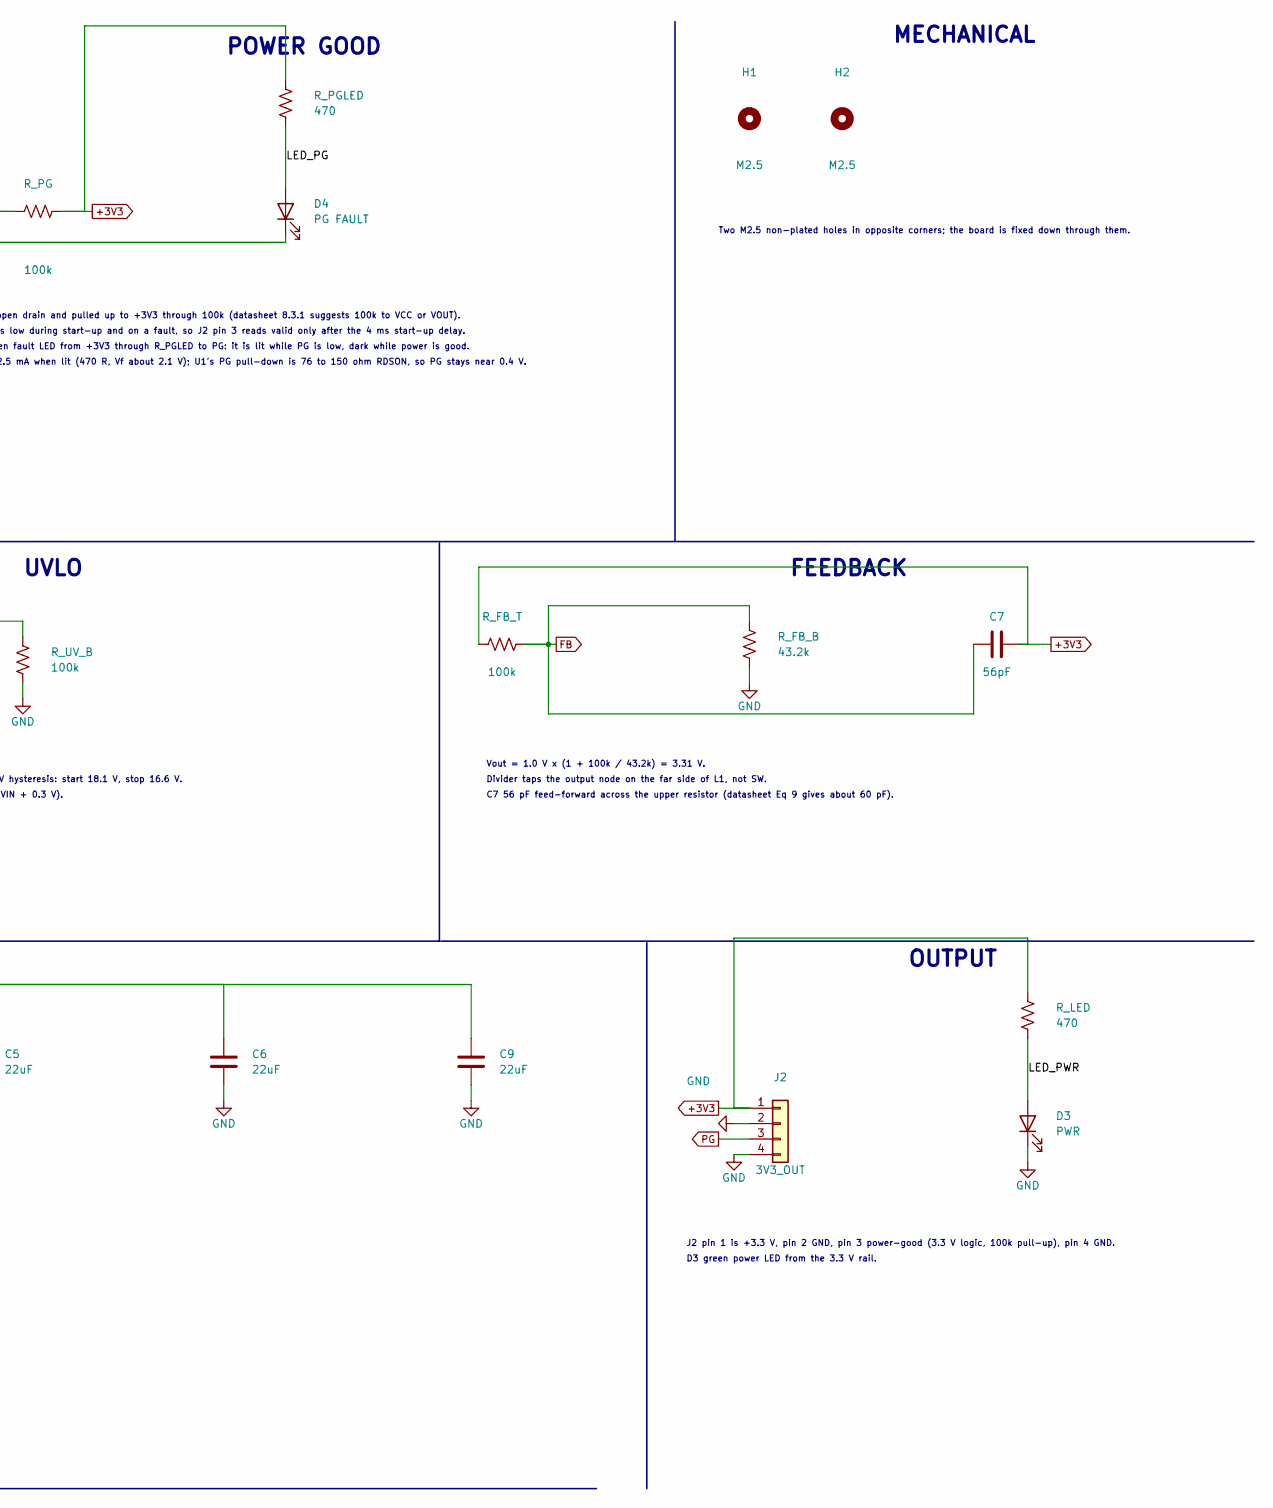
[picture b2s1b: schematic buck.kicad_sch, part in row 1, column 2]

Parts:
C1: 47uF; CP_Elec_8x10; Voltage 50V; MPN RVT1H470M0810
C2: 10uF; C_1206_3216Metric; Voltage 50V
C3: 220nF; C_0603_1608Metric; Voltage 50V
C4: 100nF; C_0603_1608Metric; Voltage 16V
C5, C6, C9: 22uF; C_1206_3216Metric; Voltage 25V
C7: 56pF; C_0603_1608Metric; Voltage 50V
C8: 1uF; C_0603_1608Metric; Voltage 16V
D1: SS36; D_SMC; MPN SS36
D2: SMBJ30A; D_SMB; MPN SMBJ30A
D3: PWR; LED_0603_1608Metric; MPN LTST-C190KGKT
D4: PG FAULT; LED_0603_1608Metric; MPN LTST-C190KGKT
F1: 1.1A_PTC; Fuse_1812_4532Metric; MPN MF-MSMF110/33X
H1, H2: M2.5; MountingHole_2.5mm
J1: 24V_IN; JST_XH_B2B-XH-A_1x02_P2.50mm_Vertical; MPN B2B-XH-A
J2: 3V3_OUT; JST_XH_B4B-XH-A_1x04_P2.50mm_Vertical; MPN B4B-XH-A
L1: 6.8uH; L_Bourns_SRN6045TA; MPN SRN6045TA-6R8M
R_FB_B: 43.2k; R_0603_1608Metric; Tolerance 1%
R_FB_T: 100k; R_0603_1608Metric; Tolerance 1%
R_LED: 470; R_0603_1608Metric
R_PG: 100k; R_0603_1608Metric
R_PGLED: 470; R_0603_1608Metric
R_UV_B: 100k; R_0603_1608Metric; Tolerance 1%
R_UV_T: 1.37M; R_0603_1608Metric; Tolerance 1%
U1: LMR33640ADDA; HSOP-8-1EP_3.9x4.9mm_P1.27mm_EP2.41x3.1mm; MPN LMR33640ADDA

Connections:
+3V3: C5.1, C6.1, C7.2, C9.1, J2.1, L1.2, R_FB_T.1, R_LED.1, R_PG.2, R_PGLED.1
BOOT: C4.1, U1.7 (BOOT)
EN: R_UV_B.1, R_UV_T.2, U1.3 (EN)
FB: C7.1, R_FB_B.1, R_FB_T.2, U1.5 (FB)
GND: C1.2, C2.2, C3.2, C5.2, C6.2, C8.2, C9.2, D2.2 (A), D3.1 (K), J1.2, J2.2, J2.4, R_FB_B.2, R_UV_B.2, U1.1 (GND), U1.9 (GND)
LED_PG: D4.2 (A), R_PGLED.2
LED_PWR: D3.2 (A), R_LED.2
PG: D4.1 (K), J2.3, R_PG.1, U1.4 (PG)
SW: C4.2, L1.1, U1.8 (SW)
U1_VCC: C8.1, U1.6 (VCC)
VIN: C1.1, C2.1, C3.1, D1.1 (K), D2.1 (K), R_UV_T.1, U1.2 (VIN)
VIN_FUSED: D1.2 (A), F1.2
VIN_RAW: F1.1, J1.1

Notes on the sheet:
INPUT PROTECTION
INPUT FILTER
UVLO
BUCK
FEEDBACK
POWER GOOD
OUTPUT
MECHANICAL
J1 pin 1 is +24 V, pin 2 is GND.
F1 resettable PTC: Ihold 1.1 A, Vmax 33 V.
D1 Schottky in series blocks reverse polarity.
D2 TVS (30 V standoff) sits after D1, directly on the VIN node. It clamps ESD and transient energy only; the clamp is above U1's absolute maximum, so it is not an OVP.
C1 bulk, C2 ceramic, C3 high-frequency next to the VIN pin (LMR33640 Table 9-2: 10 uF + 220 nF).
50 V parts for a 24 V rail; DC-bias derating of C2 is not known.
EN divider from VIN. LMR33640 VEN-H 1.231 V typical, 100 mV hysteresis: start 18.1 V, stop 16.6 V.
EN stays under 2 V at a 28 V input (EN absolute maximum is VIN + 0.3 V).
LMR33640: 400 kHz, internal compensation, exposed pad (pin 9) on GND, open-drain PG.
C4 100 nF boot capacitor between BOOT and SW; C8 1 uF on VCC.
L1 6.8 uH and 3x 22 uF follow Table 9-2 for 3.3 V at 400 kHz (minimum Cout is 3x 22 uF).
The exposed pad (pin 9) is soldered to the F.Cu GND pour. There are no vias in the pad:
the board's fabrication floor is a 0.3 mm drill and the KiCad thermal-via footprint ships 0.2 mm.
Vout = 1.0 V x (1 + 100k / 43.2k) = 3.31 V.
Divider taps the output node on the far side of L1, not SW.
C7 56 pF feed-forward across the upper resistor (datasheet Eq 9 gives about 60 pF).
PG is open drain and pulled up to +3V3 through 100k (datasheet 8.3.1 suggests 100k to VCC or VOUT).
PG goes low during start-up and on a fault, so J2 pin 3 reads valid only after the 4 ms start-up delay.
D4 green fault LED from +3V3 through R_PGLED to PG: it is lit while PG is low, dark while power is good.
About 2.5 mA when lit (470 R, Vf about 2.1 V); U1's PG pull-down is 76 to 150 ohm RDSON, so PG stays near 0.4 V.
J2 pin 1 is +3.3 V, pin 2 GND, pin 3 power-good (3.3 V logic, 100k pull-up), pin 4 GND.
D3 green power LED from the 3.3 V rail.
Two M2.5 non-plated holes in opposite corners; the board is fixed down through them.
